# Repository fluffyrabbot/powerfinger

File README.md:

# PowerFinger

**Open-source assistive input devices. Under $25 BOM. Build one for anyone who
needs it.**

PowerFinger is a family of wearable and handheld pointing devices designed for
accessibility, repairability, and surface agnosticism. Hardware design files —
schematics, PCB layouts, 3D models, BOMs, and assembly docs — are published
under CERN-OHL-S 2.0. Firmware and software, including the companion app, are
published under MIT.

**Primary validation claim:** a user with limited wrist mobility can browse,
click, drag, and scroll on everyday surfaces without host-side remapping
software.

## Philosophy

Computer input is a solved problem for people who can sit at a desk and grip a
mouse. For everyone else — people with limited wrist mobility, repetitive strain
injuries, tremors, amputations, arthritis, or simply no desk — it isn't.

Existing assistive input devices cost $100–$350 and are closed, proprietary, and
fragile. When the vendor disappears, the device becomes e-waste and the user
loses their interface to the digital world.

PowerFinger treats input devices as **prosthetics for digital agency**. The more
redundant ways people have to control things the way they find most natural, the
better as a common good. We design for:

- **Affordability.** $9–$25 BOM depending on variant. The cheapest ring is under
  $10 in components. The first two-ring validation lane targets ~$24 total.
- **Universal design.** Every device works for able-bodied users at their desk
  AND for users with specific accessibility needs. No separate "disability"
  product line.
- **Surface agnosticism as a spectrum.** The optical ring works on most opaque
  surfaces (not glass). The ball+Hall variants are intended for glass, fabric,
  and skin, but those claims stay provisional until the surface protocol is run.
  The IMU variant needs no surface at all. Each variant's limitations are
  documented honestly — see
  [docs/COMBINATORICS.md](docs/COMBINATORICS.md).
- **Composability.** One ring is a mouse. Two rings are a mouse + scroll wheel.
  Three rings are a configurable control surface. The system grows with the
  user's needs.
- **Repairability.** Every part is replaceable. 3D-print a new shell, swap a
  battery, reflash firmware. No planned obsolescence.
- **Privacy.** Fully offline operation. No cloud, no telemetry, no account. Your
  movement data stays on your device.

## Active Program

### Active Validation Lane

- `R30-OLED-NONE-NONE` optical ring pair plus `USB-HUB`
- Goal: prove the no-host-remapping cursor + click + scroll workflow first
- Source of truth: [docs/ACTIVE-LANE-CHECKLIST.md](docs/ACTIVE-LANE-CHECKLIST.md)

### Hedge Lane

- `WSTD-BALL-NONE-NONE` wand
- Use this lane only after the active ring + hub lane clears its gates or if
  the ring fails package-closure / safety reality in a way that forces a
  productization pivot

### Deferred Until Gate 6

- Ball+Hall ring
- Puck variants
- Pro optical-on-ball ring
- OCR / camera and other rich companion features
- IMU hybrids and additional mountings beyond defensive publication coverage

## Form Factors

### Ring

Every ring has a tracking sensor + a click switch + BLE. One ring is the
single-device control loop. Two identical rings plus the hub are the primary
validation lane for the no-host-remapping workflow: cursor + left click on one
finger, scroll + right click on the other. Roles are assigned in software, not
hardware.

```
Middle finger (Ring 1):  move cursor + left click
Index finger  (Ring 2):  scroll      + right click
```

Everything else — drag, double-click, zoom, middle click, modifiers — is
software-defined combinations of those four primitives.

| Variant | BOM | Surface | Resolution |
|---------|-----|---------|------------|
| Optical ring (P0) | ~$9 | Most opaque surfaces (not glass) | 800–2000 CPI |
| Ball+Hall ring (P1) | ~$11 | Target: glass, fabric, skin, and other hard cases | ~15–60 DPI |
| Optical-on-ball ring (Pro) | ~$17 | Target: any rollable surface, pending validation | Up to 12,000 CPI |

Only the optical ring is in the active validation lane. The other ring variants
remain documented for defensive publication and later research.

A USB hub dongle (~$6) is the intended path for composing two or more rings into
a single USB HID mouse without host-side remapping software.

### Wand

A pen-shaped BLE HID pointing device with a ball+Hall sensor at the tip. This
is the hedge lane: a handheld form factor designed for the surfaces and angles
that defeat optical pen mice. It is not the primary validation lane while the
ring + hub proof remains red. ~$14 BOM.

No existing product fills this space. Commercial pen mice ($35–150) use optical
sensors that fail on glass and degrade past ~20 degrees of pen tilt. Assistive
styluses only work on touchscreens. The wand is designed to work across glass,
fabric, blankets, tray tables, and other accessibility-relevant surfaces at
natural pen angles (30–70 degrees), but those claims stay gated until the
hardware protocol is run.

Pen grip reduces forearm pronation from ~42 degrees (flat mouse) to ~28 degrees
— clinically significant for carpal tunnel and RSI. An aluminum or stainless
steel body provides natural weight stabilization for tremor (same principle as
weighted assistive pens).

See [docs/WAND-COMPETITIVE.md](docs/WAND-COMPETITIVE.md) for the competitive
landscape, accessibility case, and patent analysis.

### Other Mountings

The electronics module is invariant; the harness adapts it to any body position.
The ring shell is just one harness. Others: toe ring, knuckle strap, wrist
bracelet, prosthetic mount, headband. Same PCB, same firmware, different
physical mounting. The companion app assigns meaning. These remain design-space
and defensive-publication coverage, not active implementation work.

See [docs/COMBINATORICS.md](docs/COMBINATORICS.md) for the full design space.

## Sensing Mechanisms

| Mechanism | Surface Agnostic? | Moving Parts | BOM | Resolution |
|-----------|-------------------|-------------|-----|-----------|
| Mechanical ball + Hall effect | Target: glass, fabric, skin, and other rollable surfaces | Yes | ~$2 | Low (9–36 ticks/rev) |
| Direct optical (LED) | Most opaque surfaces | None | ~$0.50–4 | Good (800–2000 CPI) |
| Direct laser (VCSEL) | More surfaces than LED | None | ~$2–5 | Good (2000+ CPI) |
| Optical on captive ball | Target: any rollable surface, pending validation | Ball only | ~$5–8 | Excellent (12K CPI) |

## Deferred Capabilities

- **OCR camera** — scan text from physical books/documents, send to companion
  app for local OCR (Tesseract/PaddleOCR), translation, or text-to-speech.
  Requires companion app; pointing function works without it. Deferred until the
  active validation lane clears Gate 4.
- **Guidance laser** — red dot on the surface shows exactly where you're
  pointing/scanning. Deferred until the active validation lane clears Gate 4.

## What Exists Today

PowerFinger is still pre-prototype, but the repo already has a real software
lane. The main difference across directories is how much of each lane is
implementation versus planning:

| Area | Current reality | Start here |
|------|-----------------|-----------|
| Firmware | Real ESP-IDF targets exist for `ring`, `hub`, `pen`, and `puck`; the verifier covers its own regression tests, host tests, companion protocol, sanitizers, active R30 profile, hub, and strict KiCad by default. | `scripts/verify-firmware-local.sh`, `docs/FIRMWARE-VERIFY-LOCAL.md` |
| Companion | A minimal local Web Serial app now lives under `companion/web/`. It talks to the hub's existing USB CDC text protocol and covers hub info, role assignment, swaps, forget, hub settings, per-ring tuning, live RSSI plus battery/diagnostics inspection, and hub-owned simultaneous-click gesture mapping. | `companion/README.md`, `companion/web/`, `docs/COMPANION-APP-ARCH.md` |
| Hardware | BOM intent files still anchor the lane, and each BOM-backed variant now has a hardware publication packet with a manifest plus assembly/disassembly baseline. The active `R30-OLED-NONE-NONE` ring and `USB-HUB` now also have first-board checklists and validation templates alongside their KiCad/OpenSCAD skeletons; routed PCBs and measured hardware evidence are still pending. | `hardware/README.md`, `hardware/bom/README.md` |
| Docs | Design, validation, accessibility, and IP docs are the most complete part of the repo today. | `docs/` |

## Quick Start

Install CMake, a C compiler, Python, Ruby, Node.js, and KiCad CLI for full local
verification. See [prerequisites and modes](docs/FIRMWARE-VERIFY-LOCAL.md).
Then install the pinned SDK and verify (reports go under `build-verification/`):

```bash
scripts/setup-esp-idf-local.sh
scripts/verify-firmware-local.sh
```

After the one-time bootstrap, `scripts/verify-firmware-local.sh` can run from a
fresh shell and will auto-activate the repo-pinned ESP-IDF 6.1 build candidate.
[Physical hardware qualification remains pending](docs/ESP-IDF-6.1-QUALIFICATION.md).
If you want `idf.py` available in your current shell for direct iteration, run:

```bash
eval "$(scripts/setup-esp-idf-local.sh --export)"
```

The shared verifier runs all mandatory local checks and builds the active
`R30-OLED-NONE-NONE` ring profile and hub. To include the generic development
ring, pen, and puck as well:

```bash
scripts/verify-firmware-local.sh --all
```

For host/contracts/operator/companion checks without SDK or hardware:

```bash
scripts/verify-firmware-local.sh --fast
```

For prerequisite diagnostics without builds:

```bash
scripts/verify-firmware-local.sh --doctor
```

For the local companion app scaffold:

```bash
scripts/serve-companion-local.sh
```

Then open `http://127.0.0.1:4173` in Chrome or Edge and connect to the hub over
Web Serial.

For hardware CAD work on macOS, prefer the current OpenSCAD snapshot cask:

```bash
brew install --cask openscad@snapshot
```

The executable remains `openscad` on `PATH`. Avoid relying on the legacy
`brew install openscad` cask path; Homebrew currently marks that older cask as
deprecated while the snapshot cask tracks the current upstream builds.

See [docs/ACTIVE-LANE-CHECKLIST.md](docs/ACTIVE-LANE-CHECKLIST.md) for the
canonical active-lane checklist, [docs/FIRMWARE-VERIFY-LOCAL.md](docs/FIRMWARE-VERIFY-LOCAL.md)
for the local verification flow, [docs/PROTOTYPE-SPEC.md](docs/PROTOTYPE-SPEC.md)
for the active build spec, [docs/COMBINATORICS.md](docs/COMBINATORICS.md) for
the broader design space, and [docs/GO-NO-GO-RUBRIC.md](docs/GO-NO-GO-RUBRIC.md)
for the validation gate order.

## Project Status

**Pre-prototype.** Architecture, design space, power budget, and competitive
analysis are documented, and the repo already contains real firmware projects
plus a local verification path. Active scope is frozen to the optical ring +
hub validation lane, with the wand as the hedge lane. The companion lane now
has a minimal local Web Serial scaffold, while the hardware tree contains BOM-
backed publication packets, service baselines, first-pass source skeletons, and
active-lane first-board checklists for the ring + hub proof path rather than
finished CAD/PCB drops. See
[docs/ACTIVE-LANE-CHECKLIST.md](docs/ACTIVE-LANE-CHECKLIST.md) for the current
program order and [docs/FIRMWARE-ROADMAP.md](docs/FIRMWARE-ROADMAP.md) for the
firmware build order that runs on dev boards before prototype hardware arrives.

## License

Three artifacts, three licenses:

- **Hardware designs** (schematics, PCB layouts, 3D models, BOMs, assembly
  docs): [CERN-OHL-S 2.0](https://opensource.org/license/cern-ohl-s)
  (strongly reciprocal). See [LICENSE-HARDWARE](LICENSE-HARDWARE).
- **Firmware and software** (ESP-IDF code, companion app): MIT.
  See [LICENSE-SOFTWARE](LICENSE-SOFTWARE).
- **Documentation** (`docs/*.md`, READMEs, assembly guides):
  [CC-BY-SA 4.0](https://creativecommons.org/licenses/by-sa/4.0/).
  See [LICENSE-DOCS](LICENSE-DOCS).

The CERN-OHL-S patent retaliation clause means anyone using these designs who
sues anyone else over them automatically loses their license. The reciprocal
requirement means anyone manufacturing products from these designs must publish
their complete source. See [docs/IP-STRATEGY.md](docs/IP-STRATEGY.md) for full
rationale.

**"PowerFinger" is used descriptively. No trademark is asserted by the
maintainers.** Anyone may build, sell, and modify the design under the
licenses above. Derivative makers are encouraged to use their own product
name and pursue [OSHWA Certified](https://certification.oshwa.org/) status as
a third-party quality signal. See
[docs/NAMING-AND-COMPATIBILITY.md](docs/NAMING-AND-COMPATIBILITY.md) for the
full naming-and-compatibility posture.

## Why "PowerFinger"?

Controlling a computer should require nothing more than a single finger. The
name is corny. It sticks.

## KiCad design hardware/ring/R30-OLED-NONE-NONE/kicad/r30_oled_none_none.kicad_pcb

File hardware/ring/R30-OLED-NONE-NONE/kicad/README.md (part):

<!-- SPDX-License-Identifier: CERN-OHL-S-2.0 -->
# R30-OLED-NONE-NONE KiCad Skeleton

This directory is the PCB/schematic starting point for the active optical ring
lane. It is intentionally honest about its state: the first routed PCB pass now
exists, and the power/USB plus MCU/radio plus sensor/click sheets now include
first-pass symbols. The current KiCad wrapper snapshot is ERC/DRC/parity clean,
but fabrication outputs and physical first-board evidence are still separate
packet gates.

## Current Source Files

- `r30_oled_none_none.kicad_sch` — root sheet for the active optical ring lane
- `r30_oled_none_none.kicad_pcb` — first rigid P0 routed board pass, with
  footprint locks, placement zones, antenna keep-outs, and charge-path routing
- `FABRICATION-OUTPUTS.md` — local Gerber/drill/POS plus active-BOM/POS review
  commands, hashes, and caveats for the DRC-clean first-board source
- `BOARD-HOUSE-OUTPUT-CONSTRAINTS.md` — prototype-house intake checklist for
  turning the local outputs into specific pre-fab feedback without claiming
  physical ring closure
- `sheets/power_and_charge.kicad_sch`
- `sheets/mcu_radio.kicad_sch`
- `sheets/sensor_and_click.kicad_sch`
- `sheets/usb_and_service.kicad_sch`

## What Belongs Here Next

- Local symbol and footprint references only where upstream libraries are not
  enough
- Plot and fabrication presets once routing exists
- `INTERFACE-CONTRACT.md` — first-pass electrical pin contract for capture and firmware
- `CAPTURE-BINDINGS.md` — which active BOM lines need stock, vendor, or custom binding
- `SCHEMATIC-CAPTURE.md` — sheet split, net naming, and capture order
- `BOM-BLOCK-MAP.md` — turn the BOM into schematic blocks without drift
- `RECOMMENDED-FIRST-CAPTURE.md` — the recommended P0 scope boundary
- `../FIRST-BOARD-CHECKLIST.md` — the execution checklist that decides when this
  packet is allowed to move on to secondary variants

## Capture Order

1. Power tree: protected LiPo, TP4054 charge path, RT9080 LDO, fixture-fed
   VBUS service jumper, NTC divider
2. MCU/module block: `ESP32-C3-MINI-1-N4` with antenna keep-out reserved first
3. Sensor block: PAW3204-class optical sensor plus matching lens and aperture
4. Human input block: dome switch and any required debounce/passive support
5. Off-board USB service/programming path for charging plus firmware bring-up

## First Routed Board Pass

`r30_oled_none_none.kicad_pcb` locks the current P0 direction:

- rigid validation board with separate power/service, sensor/click, and
  MCU/radio zones
- ESP32-C3-MINI-1 antenna end facing the shell exterior, with copper and
  antenna keep-outs marked before any convenience routing; the external
  keep-out forbids tracks, vias, pads, and copper pour while allowing the owning
  module footprint whose antenna courtyard reaches the board edge
- bottom-side PAW3204 placement centered on the `6.2 mm` optical aperture datum
  recorded as a `Cmts.User` alignment circle, not an internal `Edge.Cuts`
  fabrication cutout through the populated PCB
- off-board same-net battery service pads for a replaceable protected-cell
  harness or fixture; no onboard JST-SH receptacle body is claimed
- Off-board same-net USB service pads for USB2 data, VBUS, CC pulldowns, GND,
  and shield continuity; charge/program service now requires a fixture or pogo
  harness rather than an onboard USB-C receptacle
- TP4054 path routed through a non-BOM fixture-fed VBUS service jumper,
  `20 kohm` RPROG, RT9080 regulation, and an NTC divider near the battery
  service pads
- MCU/radio and sensor/click sheets populated with first-pass symbol
  counterparts for the routed `U1`, `U2`, `SW1`, decoupling, sense testpads,
  and sensor bring-up pads
- routed sheet nets promoted to passive global labels where they intentionally
  match flat PCB net names, with the project-local `Q1` VBUS service jumper,
  aligned USB ESD D+/D- labels, and service shield pads mapped to `SH`
- `J_BAT` backed by a project-local first-board symbol that models `MP1`/`MP2`
  as GND-tied shield/service pads, so schematic/PCB parity is clean
- first routing cleanup of USB-C SMT contact pad length, snap-dome contact
  geometry, and wrong first-pass power/USB endpoint coordinates
- second routing cleanup of the SDIO/motion fanout, VBUS-detect dogleg, long
  VBUS detector feed, and minimum routed trace width
- charger-service cleanup that replaces the active `Q1`/`R4`/`Q2`/`R6`
  charge-gate with a non-BOM fixture-fed VBUS jumper into TP4054 `VCC`
- USB/D1 fanout cleanup that nudges `D1` upward, doglegs J1 `A6`/`A7` before
  the drop, and separates the long `USB_D+`/`USB_D-` lanes into U1
- connector-edge cleanup that extends the fixed J1 service lip leftward and
  ties J1 `A4`/`A9`/`B4`/`B9` as one VBUS contact group
- connector-cluster cleanup that moves `R2B` beside J1 `B5`, shifts the local
  VBUS trunk inward, and moves `NTC1`/`R3` out of D1's immediate `USB_D+`
  corridor
- A-side USB data cleanup that moves the J1 `A6`/`A7` to D1 escape onto `B.Cu`
  under the charger cluster and re-enters beside D1 with the `USB_D-` entry via
  shifted left for clearance
- mirrored USB-C data cleanup that routes J1 `B6`/`B7` into the same escape
  through separated `B.Cu` lanes and a short front-layer `USB_D-` overpass,
  while leaving D1 VBUS disconnected because the direct branch still regresses
  total DRC; route-only D1 GND/VBUS service-island attempts also regress, so the
  follow-up needed footprint/placement movement rather than another local
  stitch
- D1 footprint cleanup that replaces the rail-clamped USBLC6 SOT-23-6 island
  with a rail-less TPD2E2U06DCK-class SC-70/SOT-323 data-line shunt, removing
  the D1 VBUS branch from the constrained service-edge pocket
- service-edge GND/shield spine that ties the J1 ground contacts and shell
  stakes, pulls `R2B` and `R1` into the lower return, reaches `J_BAT` `MP1`
  from the upper return, and drops D1/NTC ground through a local B-side via
  without reintroducing VBUS-clamped ESD protection
- battery-side GND fanout cleanup that doglegs `R8`/`J_BAT` `MP2` away from
  the `VBAT_SENSE` trace, ties `J_BAT` pad 2 into that local return, moves
  `J_BAT` `MP1` onto a B-side return via, and joins `R2A`/left `SW1`/`Q2`
  source into one local ground chain
- via-rule cleanup that brings the six remaining sub-minimum first-board vias
  from `0.46` mm diameter / `0.20` mm drill to the board-rule minimum
  `0.50` mm diameter / `0.30` mm drill
- sensor-rail cleanup that moves the `VREG_3V3` via off the PAW3204
  `SENSOR_LED_KIT`/GND pad column, routes the sensor `VDD`/`VDDA` feed down a
  right-side `B.Cu` trunk, and keeps `C1B` tied in with a short local branch
- `TP_LEDKIT` contract cleanup that supersedes the earlier PAW3204 LED test-pad
  move by deleting the non-BOM pad/stub and leaving the PAW3204 LED-kit pin as
  an explicit local no-connect
- U3 VBAT escape cleanup that routes TP4054 BAT around the GND/CHRG pad row
  through an outer dogleg before rejoining the U4 VIN trunk
- C2 input-cap placement cleanup that moves and micro-retargets the 10uF
  capacitor closer to U4 VIN while leaving its GND pad as an honest unconnected
  blocker
- B-side sensor-pocket cleanup that reroutes the `C1B` ground return around the
  PAW3204 LED pad column without moving the shell-bound PAW3204 aperture
- C1A MCU-side decoupler cleanup that moves the non-shell-bound capacitor into
  the U1 `3V3` / `GND1` pocket while leaving the shell-bound `SW1` and U1
  placements fixed
- `TP_VBAT` / right-SW1 cleanup that reroutes `VBAT_SENSE` below the top dome
  ground pad and ties the right `SW1` ring pad into the local U1/C1A ground leg
- SW1 click cleanup that reroutes `CLICK_PRIMARY_N` through a B-side via pair
  instead of through the lower dome ground pad
- C1B/U2 B-side GND cleanup that doglegs around the PAW3204 LED pad column
  without moving the shell-bound sensor aperture
- R1 charger-programming cleanup that moves non-shell-bound `R1` into a
  horizontal pocket and returns its GND pad through the accepted B-side trunk
- U4 regulator-pocket cleanup that nudges non-shell-bound U4 while preserving
  the accepted C2 placement and U3 `VBAT_PROTECTED` dogleg
- D1/NTC ground-return cleanup that moves the local GND leg through a B-side
  dogleg so it no longer shorts the `NTC_SENSE` divider trace
- `TP_VBAT` micro-retarget that moves the sense test pad upward and removes the
  upper `SW1`/`VBAT_SENSE` short
- left-service silkscreen cleanup that moves the dense `J_BAT`, `Q1`, `R8`,
  and `R2A` reference fields to `F.Fab` instead of printing clipped labels over
  the bring-up pads/copper
- `R2A` placement cleanup that moves the CC1 pull-down to `(111.650, 95.000)`
  and retargets its `USB_CC1_RD` plus GND endpoints, clearing the
  `USB_CC1_RD` / `CHARGE_GATE` short without changing ERC, unconnected count,
  or schematic/PCB parity
- `VBAT_SENSE` divider-junction cleanup that retargets the `R7`/`R8`/`TP_VBAT`
  sense trunk through `(113.000, 91.900)`, clearing the upper `SW1` dome-ring
  short without moving shell-bound `SW1` or the CAD dome pocket
- `SW1` / `VBAT_SENSE` topology cleanup that lowers the divider junction to
  `(113.000, 92.100)` and moves the serviceable dome plus shell pocket to
  `(114.200, 95.300)`, reducing total DRC while keeping shorts closed
- top-edge `VBUS_5V` trunk cleanup that retargets the VBUS feed from
  `(105.820, 91.600)` to `(105.600, 91.600)`, clearing the `J_BAT` `MP1`
  short without moving the then-shell-bound battery connector
- in-place `R9` divider flip so the right-side `VBUS_5V` trunk lands on the
  VBUS pad and `VBUS_DETECT` exits the opposite pad into the existing top node,
  plus moving `R9`'s source reference field to `F.Fab` in the copper-dense
  divider pocket
- `SW1` dome-pocket relief that moves the shell-bound click center down to
  `(114.350, 95.780)` and moves the CAD dome pocket with it; this established
  the earlier short-free topology that later ground-continuity and
  three-contact dome-ring closures brought to the current verified
  `DRC=40`, `unconnected=0`, parity `0` snapshot
- non-shell-bound `R11` / `TP_CHRG` relocation down into the charger-status
  pocket at `y=105.000`, shortening the `CHRG_STAT` run and moving their source
  reference fields to `F.Fab` in the dense regulator pocket
- top-edge source-label cleanup that keeps the accepted `VBUS_5V` /
  `VBAT_SENSE` copper after scratch retargets introduced shorting or edge debt,
  and moves the `R7`, `TP_VBAT`, and `SW1` reference fields to `F.Fab`
- charge/regulator-pocket source-label cleanup that keeps the accepted
  `CHARGE_EN`, `VREG_3V3`, and `VBAT_PROTECTED` copper after scratch retargets
  reintroduced shorting or unconnected debt, and moves the `Q2`, `U4`, and `R6`
  reference fields to `F.Fab`
- left-service source-label cleanup that keeps the accepted `USB_CC1_RD`,
  `VBUS_5V`, and `CHARGE_GATE` copper after scratch CC1/gate reroutes
  reintroduced shorting or unconnected drift, and moves the `R4` and `R1`
  reference fields to `F.Fab`
- remaining source-label cleanup that keeps the accepted `NTC_SENSE`,
  `VREG_3V3`, and `CHRG_STAT` copper after scratch reroutes raised total DRC or
  reintroduced shorting, and moves the remaining source-only silkscreen marks
  to `F.Fab`/`B.Fab`
- pad-mask expansion cleanup that keeps `solder_mask_min_width=0.05` but
  changes first-board pad mask expansion from `0.05` to `0`, reducing
  mask-bridge rows without relaxing the minimum mask-web rule
- regulator/C2 spoke-width cleanup that keeps U4 and C2 placement fixed after
  scratch placement variants reintroduced shorts or held total DRC, and narrows
  the two `VBAT_PROTECTED` spokes from `0.32` to `0.24`
- Q1 left-service cleanup that rejects R4 orientation, CC1 dogleg, and
  top-edge `VBUS_5V`/`VBAT_SENSE` variants with unconnected, shorting, or
  copper-edge debt, then nudges Q1 upward by a retained total `0.30` mm and
  retargets its three local service endpoints
- TP_VBAT top power-pocket cleanup that rejects regulator width, R11/TP_CHRG,
  U4, R6, C2 GND, C1A, and layer-hop probes that held total DRC or added debt,
  then nudges `TP_VBAT` right by `0.10` mm and retargets its two local
  `VBAT_SENSE` endpoints
- SENSOR_SCLK MCU-column cleanup that rejects direct SCLK, top-dogleg SCLK,
  `VBUS_DETECT`, and `SENSOR_MOTION_N` route variants with shorts or clearance
  debt, then raises the local SCLK jog from `y=99.900` to `y=99.980`
- TP_MOT MCU-column cleanup that rejects VBUS spine, VBUS dogleg, B-side
  motion-hop, and right-of-VBUS `TP_MOT` variants with dangling vias, shorts,
  mask, or clearance debt, then moves `TP_MOT` to `(121.250, 99.500)` and
  retargets its local `SENSOR_MOTION_N` endpoint
- NTC sense-spine cleanup that rejects USB data-pair and broad `NTC_SENSE`
  trunk/layer-hop variants with shorts, clearance, mask, or track-width debt,
  then moves only the local `NTC_SENSE` junction from `(110.420, 106.700)` to
  `(109.900, 106.700)`
- Left-service CC2 pulldown cleanup that rejects VBUS doglegs, VBUS junction
  moves, and broad R2B shifts with shorts, copper-edge, hole-clearance, mask, or
  extra clearance debt, then moves only `R2B` from `(100.500, 101.500)` to
  `(100.400, 101.500)` and retargets its local `USB_CC2_RD` and GND endpoints
- GND-continuity cleanup that keeps the shell-bound placements and schematic
  contracts intact while closing six unconnected rows: a lower `SW1` local GND
  stitch, via-assisted U3 and C2 returns, a via-assisted `J_BAT` pad-2 return,
  a left-trunk B-side bridge, and a C2-to-U1-side GND return; direct `J1` A12
  and top-`SW1` closure variants were rejected because they reintroduced
  current shorting rows
- `J1` A12 service-ground cleanup that closes the lower USB-C ground row from
  the existing lower GND rail endpoint to the accepted service-edge via while
  leaving the USB-D- fanout intact; top-`SW1` closure remains blocked by the
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
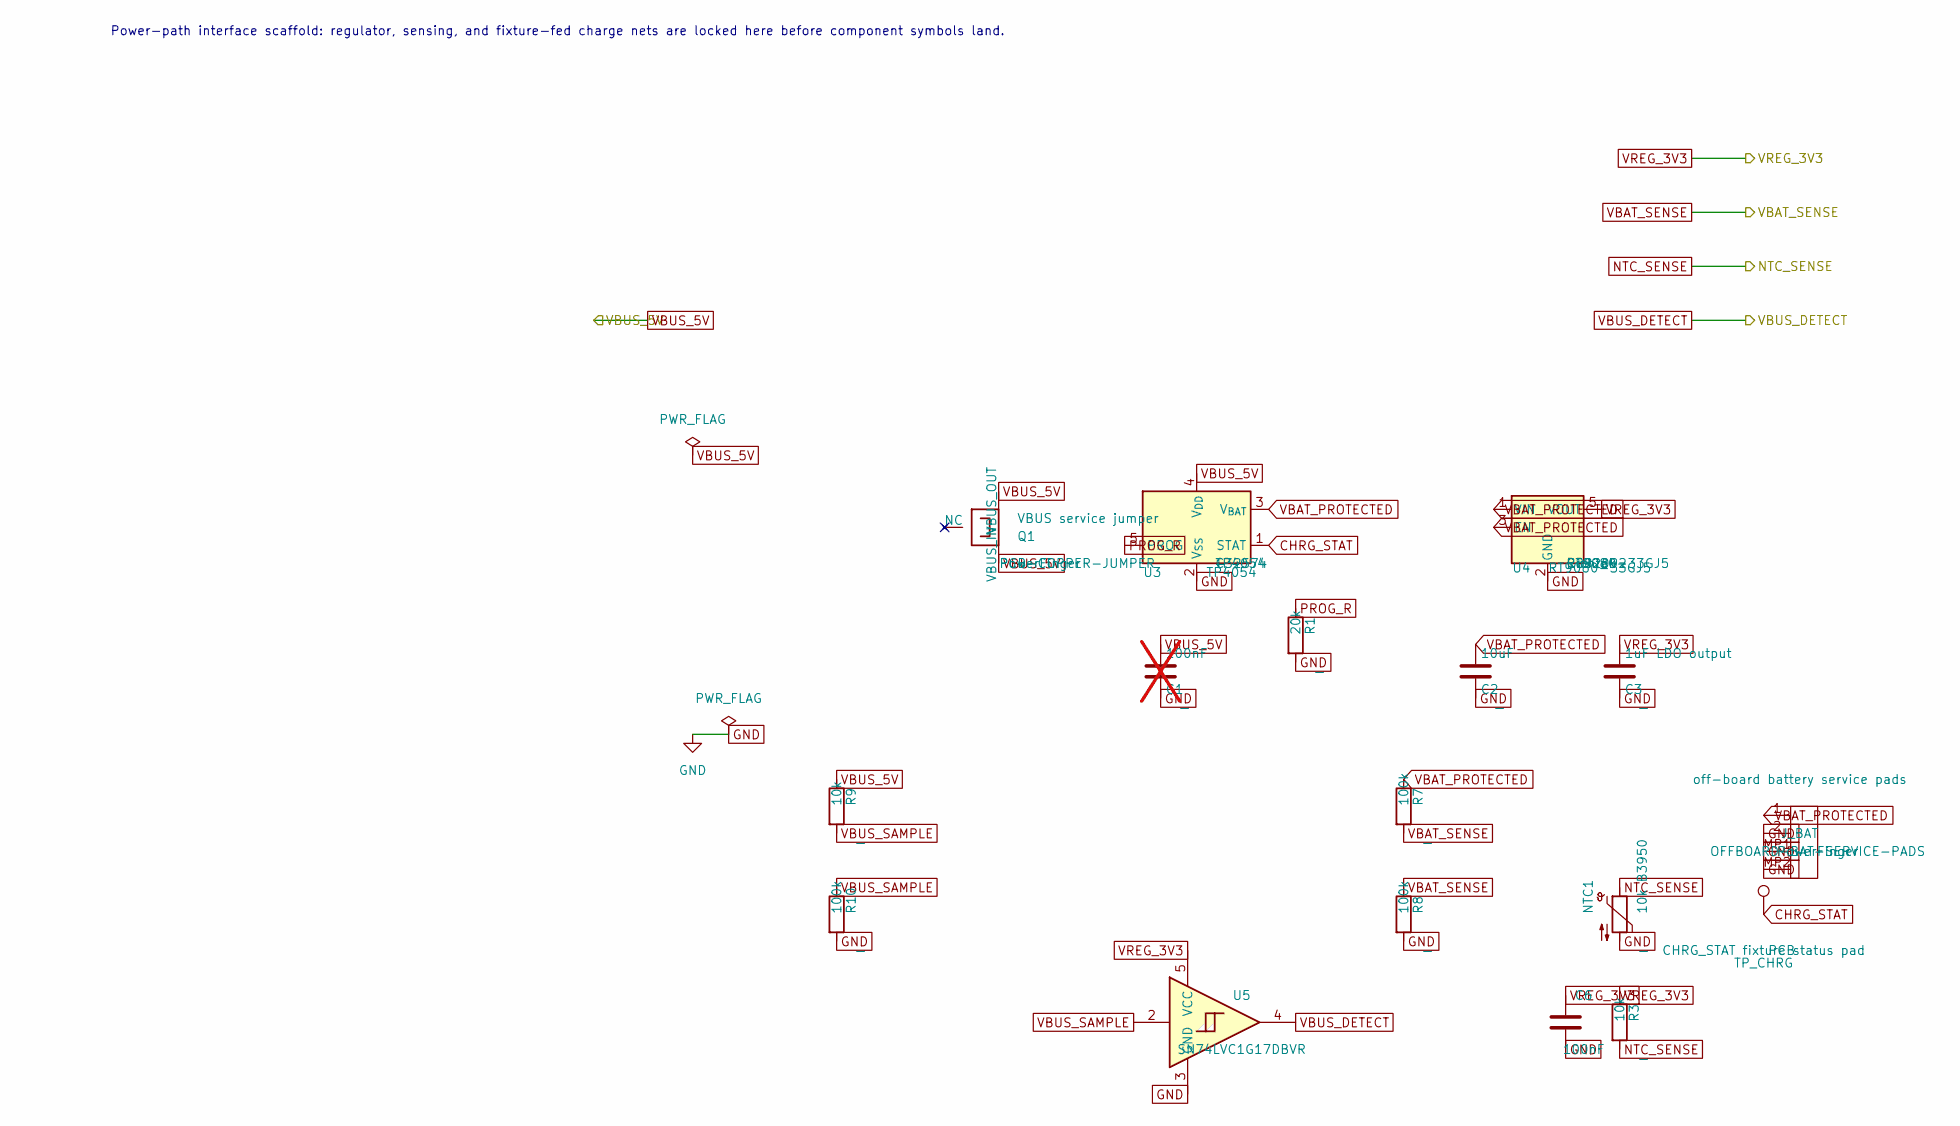
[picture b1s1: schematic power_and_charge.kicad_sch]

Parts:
C1: 100nF; C_0402_1005Metric; not fitted
C2: 10uF; C_0603_1608Metric
C3: 1uF LDO output; C_0603_1608Metric
C6: 100nF; C_0402_1005Metric
J_BAT: off-board battery service pads; Offboard_Battery_Service_SameNet; mfg_part_num OFFBOARD-BAT-SERVICE-PADS
NTC1: 10k B3950; Thermistor_NTC_0402_1005Metric
Q1: VBUS service jumper; VBUS_Service_Jumper_SOT23Land; mfg_part_num PCB-COPPER-JUMPER
R1: 20k; R_0402_1005Metric
R3, R9: 10k; R_0402_1005Metric
R7, R8, R10: 100k; R_0402_1005Metric
TP_CHRG: CHRG_STAT fixture status pad; TestPoint_Pad_D1.0mm_FirstBoard
U3: TP4054; SOT-23-5; mfg_part_num TP4054; lcsc C32574
U4: RT9080-33GJ5; RT9080_33GJ5_SOT23_5_ServiceClearance; mfg_part_num RT9080-33GJ5; lcsc C882092
U5: SN74LVC1G17DBVR; SOT-23-5

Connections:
CHRG_STAT: TP_CHRG.1, U3.1 (CHRG)
NTC_SENSE: NTC1.1, R3.2; also elsewhere on the board
PROG_R: R1.1, U3.5 (PROG)
VBAT_PROTECTED: C2.1, J_BAT.1 (VBAT+), R7.1, U3.3 (BAT), U4.1 (VIN), U4.3 (EN)
VBAT_SENSE: R7.2, R8.1; also elsewhere on the board
VBUS_DETECT: U5.4; also elsewhere on the board
VBUS_SAMPLE: R9.2, R10.1, U5.2
VREG_3V3: C3.1, C6.1, R3.1, U4.5 (VOUT), U5.5 (VCC); also elsewhere on the board

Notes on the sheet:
Power-path interface scaffold: regulator, sensing, and fixture-fed charge nets are locked here before component symbols land.

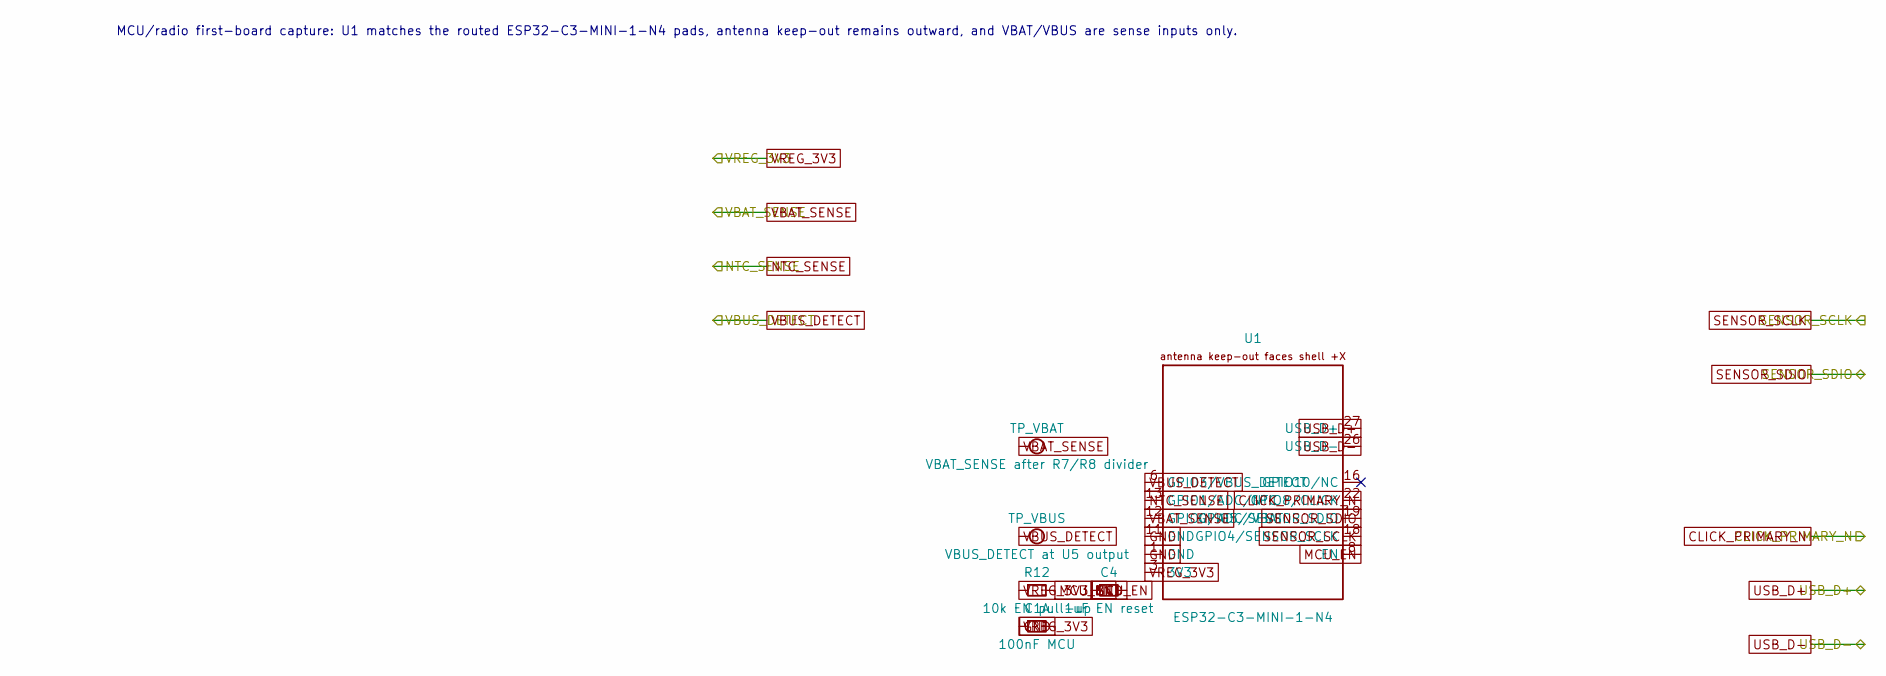
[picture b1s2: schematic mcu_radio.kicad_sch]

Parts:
C1A: 100nF MCU; C_0402_1005Metric
C4: 1uF EN reset; C_0603_1608Metric
R12: 10k EN pull-up; R_0402_1005Metric
TP_VBAT: VBAT_SENSE after R7/R8 divider; TestPoint_Pad_D1.0mm
TP_VBUS: VBUS_DETECT at U5 output; TestPoint_Pad_D1.0mm
U1: ESP32-C3-MINI-1-N4; ESP32-C3-MINI-1_N4_Module_P0_AntennaRight

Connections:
CLICK_PRIMARY_N: U1.22 (GPIO8/CLICK); also elsewhere on the board
MCU_EN: C4.1, R12.2, U1.8 (EN)
NTC_SENSE: U1.13 (GPIO1/ADC/NTC); also elsewhere on the board
SENSOR_SCLK: U1.18 (GPIO4/SENSOR_SCLK); also elsewhere on the board
SENSOR_SDIO: U1.19 (GPIO5/SENSOR_SDIO); also elsewhere on the board
USB_D+: U1.27 (USB_D+); also elsewhere on the board
USB_D-: U1.26 (USB_D-); also elsewhere on the board
VBAT_SENSE: TP_VBAT.1, U1.12 (GPIO0/ADC/VBAT); also elsewhere on the board
VBUS_DETECT: TP_VBUS.1, U1.6 (GPIO3/VBUS_DETECT); also elsewhere on the board
VREG_3V3: C1A.1, R12.1, U1.3 (3V3); also elsewhere on the board

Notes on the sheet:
MCU/radio first-board capture: U1 matches the routed ESP32-C3-MINI-1-N4 pads, antenna keep-out remains outward, and VBAT/VBUS are sense inputs only.

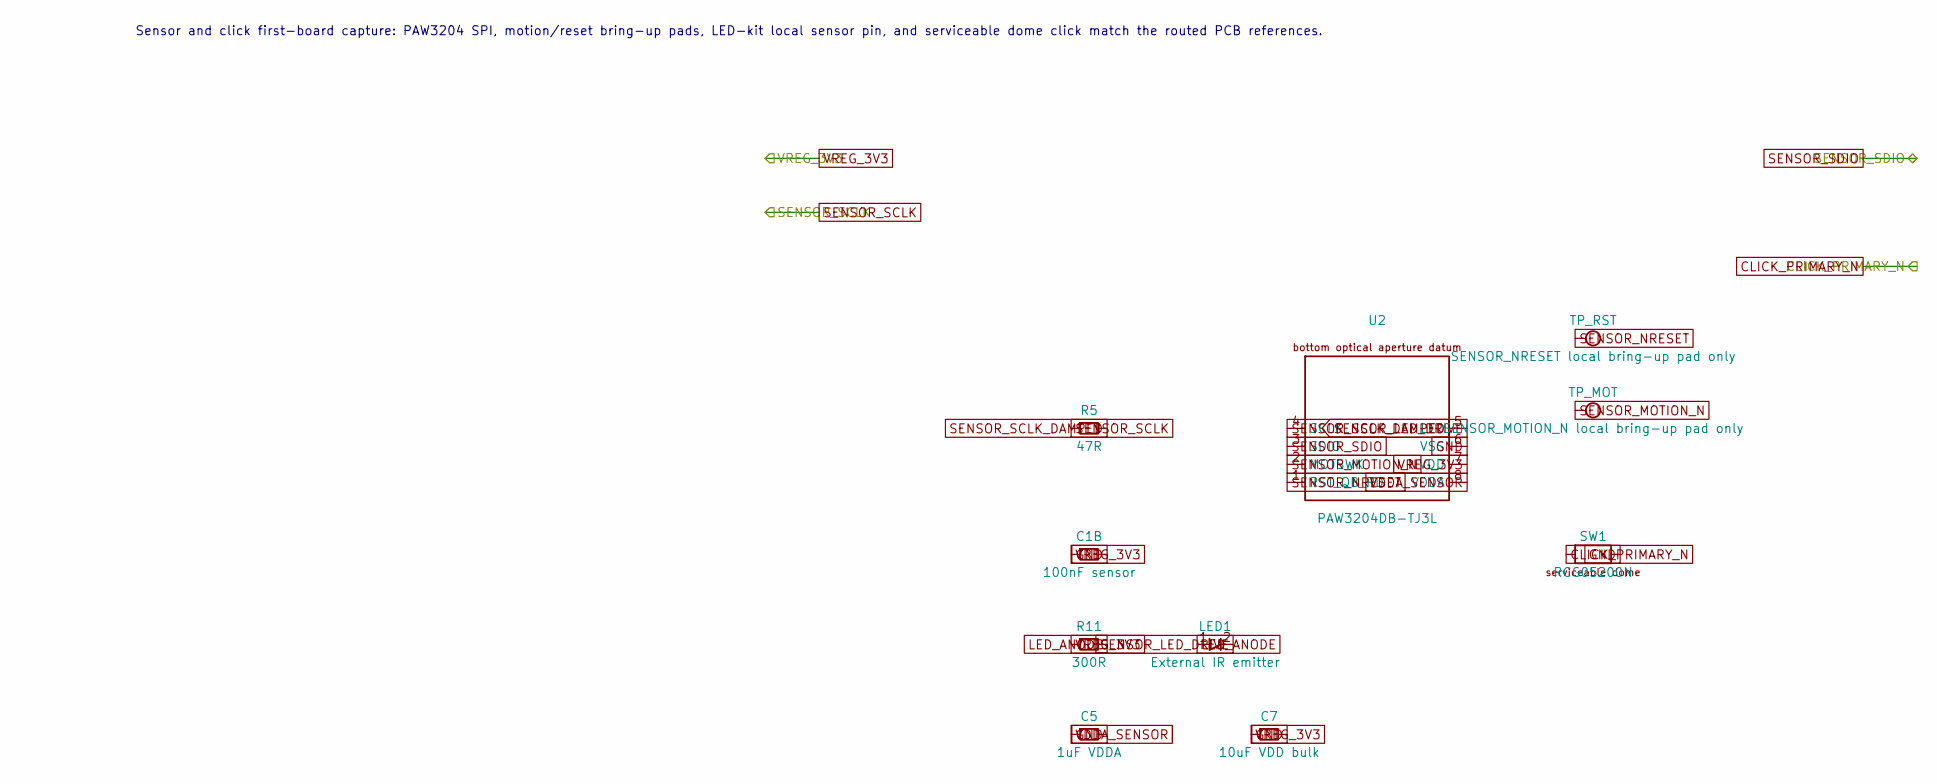
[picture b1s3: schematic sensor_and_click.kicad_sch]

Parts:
C1B: 100nF sensor; C_0402_1005Metric
C5: 1uF VDDA; C_0402_1005Metric
C7: 10uF VDD bulk; C_0603_1608Metric
LED1: External IR emitter; IR_Emitter_Lead_Pads
R5: 47R; R_0402_1005Metric
R11: 300R; R_0402_1005Metric
SW1: RCG05200N; Snap_Dome_5mm_TwoPad_Serviceable
TP_MOT: SENSOR_MOTION_N local bring-up pad only; TestPoint_Pad_D1.0mm
TP_RST: SENSOR_NRESET local bring-up pad only; TestPoint_Pad_D1.0mm
U2: PAW3204DB-TJ3L; PAW3204DB_TJ3L_Staggered_DIP8_Bottom_ApertureDatum

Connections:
CLICK_PRIMARY_N: SW1.1 (DOME_CENTER); also elsewhere on the board
LED_ANODE: LED1.1 (A), R11.2
SENSOR_LED_DRIVE: LED1.2 (K), U2.5 (LED)
SENSOR_MOTION_N: TP_MOT.1, U2.2 (MOTSWK)
SENSOR_NRESET: TP_RST.1, U2.1 (RST_QB_PD)
SENSOR_SCLK: R5.1; also elsewhere on the board
SENSOR_SCLK_DAMPED: R5.2, U2.4 (SCLK)
SENSOR_SDIO: U2.3 (SDIO); also elsewhere on the board
VDDA_SENSOR: C5.1, U2.8 (VDDA)
VREG_3V3: C1B.1, C7.1, R11.1, U2.7 (VDD); also elsewhere on the board

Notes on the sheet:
Sensor and click first-board capture: PAW3204 SPI, motion/reset bring-up pads, LED-kit local sensor pin, and serviceable dome click match the routed PCB references.

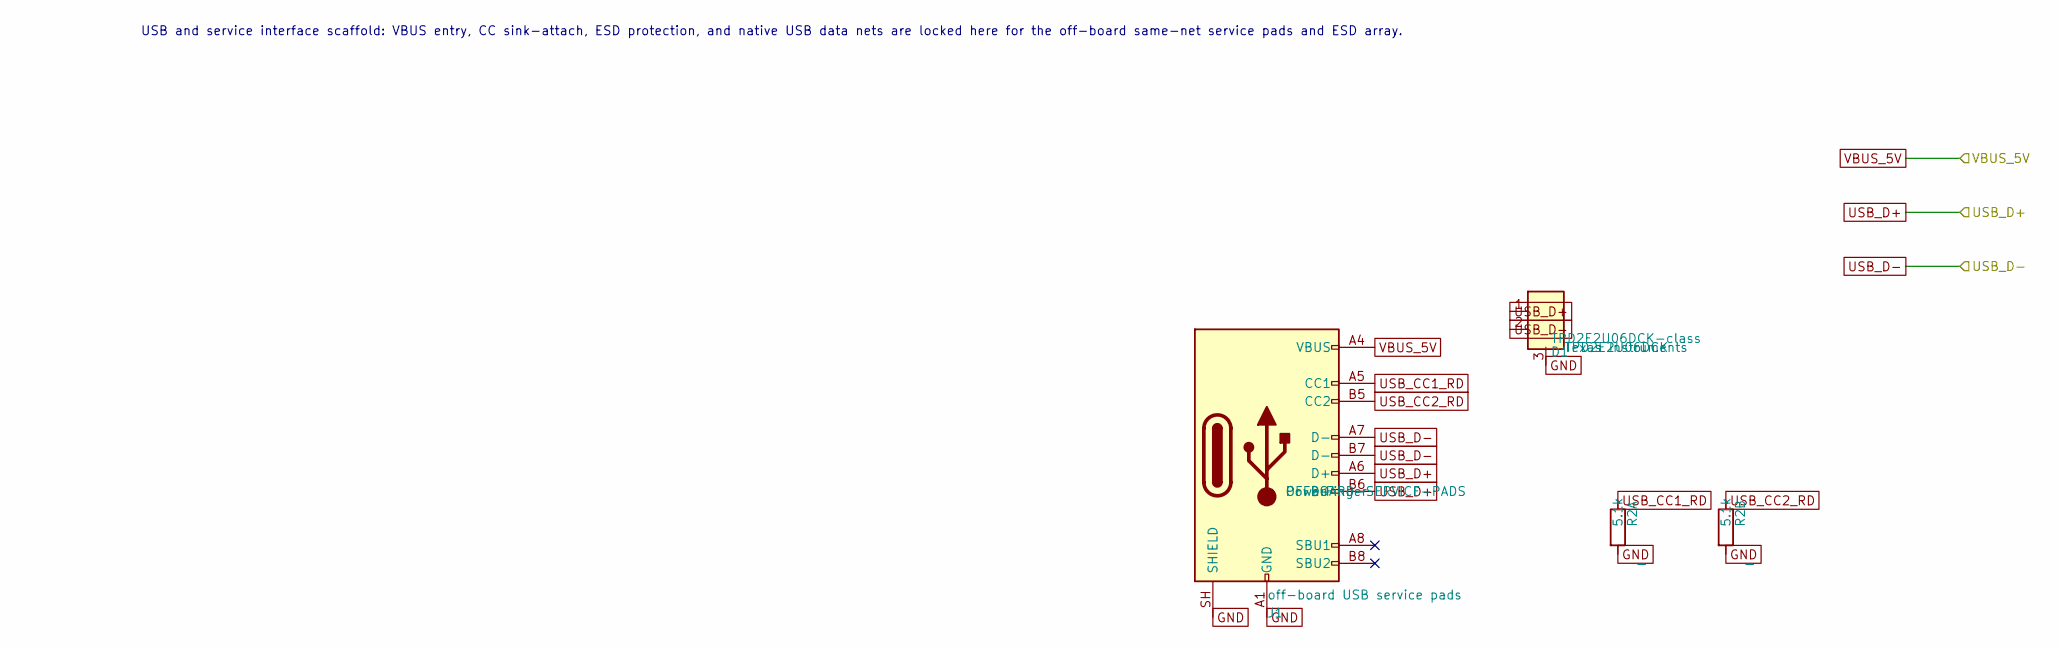
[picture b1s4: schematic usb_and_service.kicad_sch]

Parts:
D1: TPD2E2U06DCK-class; SOT-323_SC-70; mfg_part_num TPD2E2U06DCK
J1: off-board USB service pads; Offboard_USB_Service_SameNet; mfg_part_num OFFBOARD-SERVICE-PADS
R2A, R2B: 5.1k; R_0402_1005Metric

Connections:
USB_CC1_RD: J1.A5 (CC1), R2A.1
USB_CC2_RD: J1.B5 (CC2), R2B.1
USB_D+: D1.1 (IO1), J1.A6 (D+), J1.B6 (D+); also elsewhere on the board
USB_D-: D1.2 (IO2), J1.A7 (D-), J1.B7 (D-); also elsewhere on the board

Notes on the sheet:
USB and service interface scaffold: VBUS entry, CC sink-attach, ESD protection, and native USB data nets are locked here for the off-board same-net service pads and ESD array.

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
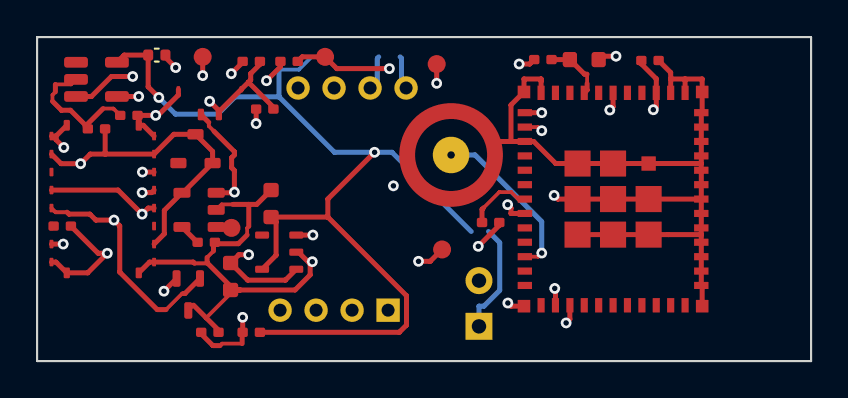
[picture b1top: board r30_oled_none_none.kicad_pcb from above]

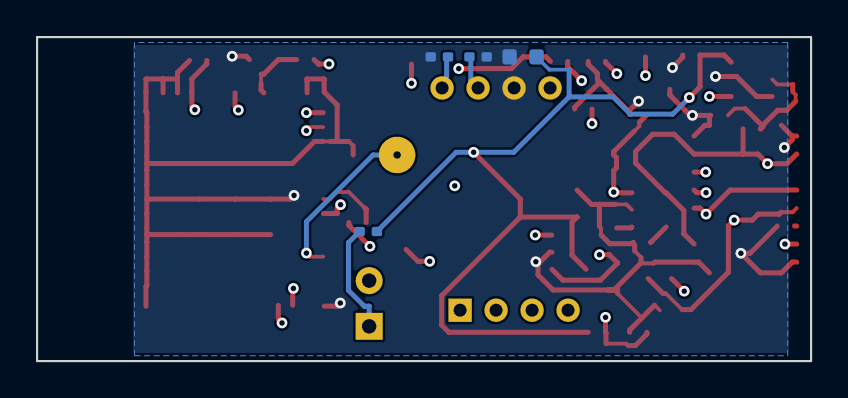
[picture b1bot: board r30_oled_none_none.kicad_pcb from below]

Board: 4 copper layers, 43.0 x 18.0 mm, 36 parts (6 on the bottom side), 24 nets.

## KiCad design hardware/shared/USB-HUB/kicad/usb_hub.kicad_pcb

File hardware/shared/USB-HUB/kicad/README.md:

<!-- SPDX-License-Identifier: CERN-OHL-S-2.0 -->
# USB-HUB KiCad Packet

This directory is the schematic/layout starting point for the active hub
accessory lane.

The packet now includes a first routed board-source pass. It is still a first
board, not measured hardware evidence: connector strain, host clearance, and
enclosure fit must be validated before the lane moves to secondary variants.

## Current Source Files

- `usb_hub.kicad_sch` — root sheet for the active hub lane
- `sheets/usb_and_power.kicad_sch`
- `sheets/mcu_radio.kicad_sch`
- `sheets/controls_and_indicators.kicad_sch`
- `usb_hub.kicad_pcb` — stepped USB-A direct-plug first-board pass
- `usb_hub.kicad_pro` — local KiCad project settings for this packet
- `sym-lib-table` — local project symbol table for KiCad CLI/library checks
- `PowerFinger.kicad_sym` — local hub-specific first-board symbols
- `fp-lib-table` — local project footprint table for KiCad CLI/library checks
- `PowerFinger_USB.pretty/` — local footprint library for the direct-plug USB-A
  connector, first-board ESP32-S3 module land pattern, service pads, clamp
  holes, and packet-pinned commodity footprints
- `FABRICATION-OUTPUTS.md` — checked-in note for regenerating and reviewing the
  local Gerber, drill, POS, active-BOM/POS, and archive outputs
- `BOARD-HOUSE-OUTPUT-CONSTRAINTS.md` — board-house intake questions tied to
  the current generated-output state

## What Belongs Here Next

- `INTERFACE-CONTRACT.md` — first-pass native USB and recovery-pin contract
- `BRINGUP-SERVICE-MATRIX.md` — mandatory recovery access and first-board checks
- `CAPTURE-BINDINGS.md` — which active BOM lines need stock, vendor, or custom binding
- `P0-COMPONENT-LOCKS.md` — exact first-board USB and power parts for the active dongle lane
- `SCHEMATIC-CAPTURE.md` — sheet split, net naming, and capture order
- `BOM-BLOCK-MAP.md` — map the BOM into the first hub schematic
- `RECOMMENDED-FIRST-CAPTURE.md` — the recommended first board scope
- `../FIRST-BOARD-CHECKLIST.md` — the execution checklist that decides when this
  packet is allowed to move on to secondary variants

## Capture Order

1. Native USB path and `VBUS_5V` entry from the connector
2. `RT9080-33GJ5` 5V-to-3.3V regulation, decoupling, and connector-side protection
3. Boot/reset and bring-up access
4. Status LED and any test pads

## First Board Reality

- The current PCB outline is stepped: the USB-A nose carries the SOFNG USB-05
  shell-tab pads and widens to a `54 x 26 mm` module/service body behind the
  plug. That is more honest than the earlier placeholder, but adjacent-port
  host clearance is now an explicit mechanical risk to verify.
- `R1` is resolved as two 22R 0402 resistors (`R1A`, `R1B`) placed at the
  ESP32-S3 side of the native USB pair. `C5` / `C6` remain unconnected
  no-BOM 0402 mechanical placeholders in this pass; shunt capacitors are not
  part of the clean first-board routing until SI evidence calls for them.
- `U1` is rotated so the ESP32-S3 antenna keep-out lands at the rear of the
  dongle, away from the USB shell and away from service pads.
- `SW1` is a pad-actuated `BOOT_N` service path for this pass; `EN`, `BOOT_N`,
  UART0, power, and ground pads remain probeable along the reopenable seam.
  USB data continuity is inspected at trace/connector access points rather than
  dedicated connected USB data service pads in this pass. `TP6`-`TP9` are now
  explicit no-BOM schematic service pads matching the routed board footprints.
- The schematic now carries the routed board's common ground, EN RC support,
  status LED path, and local decoupling instead of leaving those as PCB-only
  drift. The USB shell tabs and ESP32-S3 module ground pads are now explicit
  schematic pins tied to ground, and PCB footprint metadata matches the locked
  schematic fields. KiCad CLI verification is active on this packet: the current
  schematic ERC and PCB DRC pass at error severity with local symbol and
  footprint libraries loaded, the all-severity schematic ERC reports 0
  messages, and the all-severity PCB DRC pass is clean with 0 unconnected items
  and 0 schematic parity issues.
  `usb_hub.kicad_pro` intentionally ignores `lib_footprint_mismatch` because
  the first-board footprints are now source-controlled in
  `PowerFinger_USB.pretty/`; the remaining blockers are measured hardware
  evidence, not KiCad ERC/DRC drift.
- Local fabrication-review outputs are generated by
  `scripts/generate-usb-hub-fabrication-review.py` under
  `build-kicad/USB-HUB/fabrication-review/`. `FABRICATION-OUTPUTS.md` records
  the current output hashes and the active-BOM/POS review status; those outputs
  are reproducible review artifacts, not source-controlled fabrication release
  proof.

## Hard Constraints

- Native USB is load-bearing for the hub. Do not insert an unnecessary USB-UART
  bridge into the normal data path.
- Treat [PLACEMENT-CONSTRAINTS.md](PLACEMENT-CONSTRAINTS.md) as a blocker list.
- Connector mechanical support matters as much as the schematic.
- `VREG_3V3` must be generated by the captured board power tree, not borrowed
  from a hidden dev-board assumption.
- The current P0 path locks `J1`, `U2`, and `D1`; those exact parts are now
  represented in schematic and PCB source.
- `usb_and_power.kicad_sch` now contains the locked USB/power symbols plus the
  `R1A` / `R1B` 22R native-USB decision.
- The first PCB source captures connector reinforcement geometry, but that is
  not a substitute for the retention evidence in
  `../CONNECTOR-RETENTION-VERIFY.md`.
- Close `../FIRST-BOARD-CHECKLIST.md` and
  `../CONNECTOR-RETENTION-VERIFY.md` before treating this lane as hardware-ready.

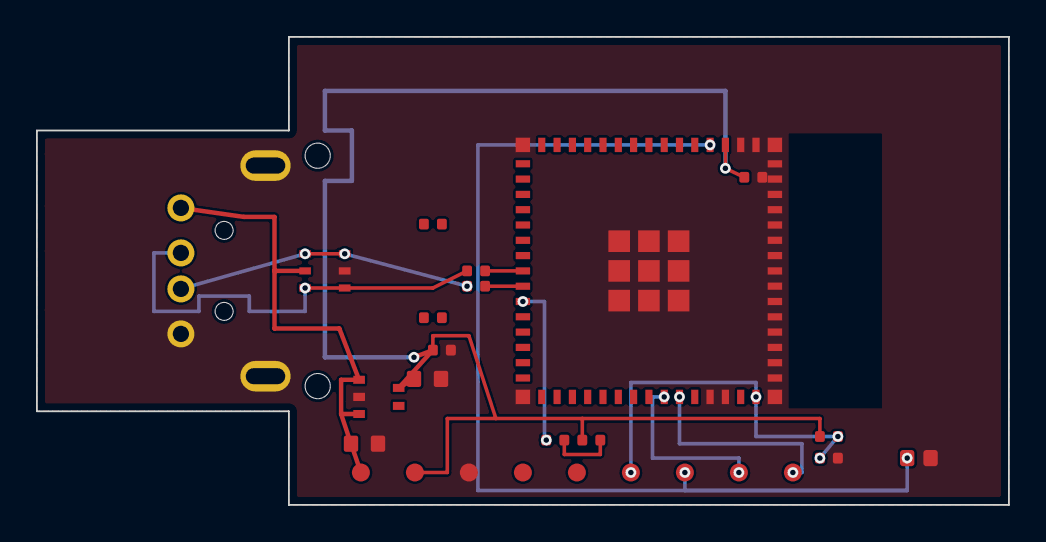
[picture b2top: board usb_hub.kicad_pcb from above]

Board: 2 copper layers, 54.0 x 26.0 mm, 28 parts (0 on the bottom side), 13 nets.

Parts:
C1A, C1B: 100nF; C_0402_1005Metric_FirstBoard
C2: 10uF; C_0603_1608Metric_FirstBoard
C3: 1uF; C_0603_1608Metric_FirstBoard
C4: 1uF; C_0402_1005Metric_FirstBoard
C5: DNI USB_D- no-net; C_0402_1005Metric_FirstBoard
C6: DNI USB_D+ no-net; C_0402_1005Metric_FirstBoard
D1: USBLC6-2SC6; SOT-23-6_FirstBoard
J1: SOFNG USB-05; USB_A_Plug_SOFNG_USB-05
LED1: green; LED_0402_1005Metric_FirstBoard
MH1, MH2: shell clamp; MountingHole_1.4mm_Clamp
R1A, R1B: 22R; R_0402_1005Metric_FirstBoard
R2: 1k; R_0402_1005Metric_FirstBoard
R3: 10k; R_0402_1005Metric_FirstBoard
SW1: BOOT_SERVICE; PadActuated_Boot_Service
TP1: VBUS; TestPoint_Pad_D1.0mm_FirstBoard
TP2: 3V3; TestPoint_Pad_D1.0mm_FirstBoard
TP3: GND; TestPoint_Pad_D1.0mm_FirstBoard
TP4: D- trace access; TestPoint_Pad_D1.0mm_FirstBoard
TP5: D+ trace access; TestPoint_Pad_D1.0mm_FirstBoard
TP6: EN; TestPoint_Pad_D1.0mm_FirstBoard
TP7: BOOT; TestPoint_Pad_D1.0mm_FirstBoard
TP8: TX; TestPoint_Pad_D1.0mm_FirstBoard
TP9: RX; TestPoint_Pad_D1.0mm_FirstBoard
U1: ESP32-S3-MINI-1-N8; ESP32-S3-MINI-1-N8_FirstBoard
U2: RT9080-33GJ5; SOT-23-5_FirstBoard

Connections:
/controls_and_indicators/BOOT_N: SW1.1, TP7.1, U1.4
/controls_and_indicators/EN: C4.1, R3.2, TP6.1, U1.45
/controls_and_indicators/GND: C1A.2, C1B.2, C2.1, C3.1, C4.2, D1.2, J1.4, J1.SH1, J1.SH2, SW1.2, TP3.1, U1.1, U1.2, U1.42, U1.43, U1.46, U1.47, U1.48, U1.49, U1.50, U1.51, U1.52, U1.53, U1.54, U1.55, U1.56, U1.57, U1.58, U1.59, U1.60, U1.61, U1.62, U1.63, U1.64, U1.65, U2.2
/controls_and_indicators/LED_LIMIT: LED1.2, R2.2
/controls_and_indicators/LED_STATUS: LED1.1, U1.25
/controls_and_indicators/UART_RX_DBG: TP9.1, U1.40
/controls_and_indicators/UART_TX_DBG: TP8.1, U1.39
/controls_and_indicators/VREG_3V3: C1A.1, C1B.1, C3.2, R2.1, R3.1, TP2.1, U1.3, U2.5
/mcu_radio/USB_D+: R1B.2, U1.24
/mcu_radio/USB_D-: R1A.2, U1.23
/usb_and_power/USB_D+_CONN: D1.3, D1.4, J1.3, R1B.1
/usb_and_power/USB_D-_CONN: D1.1, D1.6, J1.2, R1A.1
/usb_and_power/VBUS_5V: C2.2, D1.5, J1.1, TP1.1, U2.1, U2.3

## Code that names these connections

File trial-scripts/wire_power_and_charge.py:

# SPDX-License-Identifier: MIT
"""Trial driver: wire R30 power_and_charge sub-sheet via kicad-sch-api.

Strategy: place a wire label at every component pin position, naming the
net. KiCad treats same-named labels on a sheet as one net. Hierarchical
labels (VBUS_5V, VREG_3V3, VBAT_SENSE, NTC_SENSE, CHARGE_EN) already exist
and are matched by name.

Internal nets:
  VBUS_CHG       — Q1.D → U3.VCC (TP4054 input via P-MOSFET high-side switch)
  Q1_GATE        — Q1.G ← R4 pull-up to VBUS_5V; Q2.D pulls low when CHARGE_EN
  VBAT_PROTECTED — TP4054.BAT → battery rail → U4.VIN/EN, divider tops
  U3_PROG        — TP4054.PROG → R1 → GND (charge current set)
  CHRG_STAT_INT  — TP4054.STAT (open-drain) → R11 pull-up to VREG_3V3
  VBUS_DETECT_INT — R9/R10 divider mid-point (no parent sheet pin yet)
"""
from __future__ import annotations

import sys
from pathlib import Path

import kicad_sch_api as ksa

SHEET = (
    "hardware/ring/R30-OLED-NONE-NONE/kicad/sheets/power_and_charge.kicad_sch"
)

# (ref, pin_number, net_name) — None means leave unconnected (NC pin)
TOPOLOGY = [
    # Q1 — P-MOSFET high-side switch (S=VBUS_5V, D=VBUS_CHG, G=Q1_GATE)
    ("Q1", "S", "VBUS_5V"),
    ("Q1", "D", "VBUS_CHG"),
    ("Q1", "G", "Q1_GATE"),
    # Q2 — N-MOSFET low-side gate driver
    ("Q2", "D", "Q1_GATE"),
    ("Q2", "S", "GND"),
    ("Q2", "G", "CHARGE_EN"),
    # R4 — Q1 gate pull-up to VBUS_5V (default-off)
    ("R4", "1", "VBUS_5V"),
    ("R4", "2", "Q1_GATE"),
    # R6 — Q2 gate pulldown to GND (default-off)
    ("R6", "1", "CHARGE_EN"),
    ("R6", "2", "GND"),
    # U3 — TP4054 (MCP73831-2-OT pinout: STAT=1, VSS=2, VBAT=3, VDD=4, PROG=5)
    ("U3", "1", "CHRG_STAT_INT"),
    ("U3", "2", "GND"),
    ("U3", "3", "VBAT_PROTECTED"),
    ("U3", "4", "VBUS_CHG"),
    ("U3", "5", "U3_PROG"),
    # R1 — TP4054 charge current set (20k → ~50mA)
    ("R1", "1", "U3_PROG"),
    ("R1", "2", "GND"),
    # R11 — CHRG_STAT pull-up
    ("R11", "1", "VREG_3V3"),
    ("R11", "2", "CHRG_STAT_INT"),
    # U4 — RT9080 LDO (AP2112K pinout: VIN=1, GND=2, EN=3, NC=4, VOUT=5)
    ("U4", "1", "VBAT_PROTECTED"),
    ("U4", "2", "GND"),
    ("U4", "3", "VBAT_PROTECTED"),  # EN tied to VIN (always enabled)
    # U4.4 = NC, intentionally unlabeled
    ("U4", "5", "VREG_3V3"),
    # C1 — TP4054 input decoupling
    ("C1", "1", "VBUS_CHG"),
    ("C1", "2", "GND"),
    # C2 — LDO input bulk
    ("C2", "1", "VBAT_PROTECTED"),
    ("C2", "2", "GND"),
    # C3 — LDO output decoupling
    ("C3", "1", "VREG_3V3"),
    ("C3", "2", "GND"),
    # R7/R8 — VBAT_SENSE divider (100k/100k, top to VBAT_PROTECTED)
    ("R7", "1", "VBAT_PROTECTED"),
    ("R7", "2", "VBAT_SENSE"),
    ("R8", "1", "VBAT_SENSE"),
    ("R8", "2", "GND"),
    # R9/R10 — VBUS_DETECT divider (220k/100k, top to VBUS_5V)
    ("R9", "1", "VBUS_5V"),
    ("R9", "2", "VBUS_DETECT_INT"),
    ("R10", "1", "VBUS_DETECT_INT"),
    ("R10", "2", "GND"),
    # R3 — NTC divider top from VREG_3V3
    ("R3", "1", "VREG_3V3"),
    ("R3", "2", "NTC_SENSE"),
    # NTC1 — divider bottom to GND
    ("NTC1", "1", "NTC_SENSE"),
    ("NTC1", "2", "GND"),
]


def main() -> int:
    repo = Path(__file__).resolve().parent.parent
    sheet_path = repo / SHEET
    sch = ksa.load_schematic(str(sheet_path))
    print(f"loaded {sheet_path}")

    # collect U4 NC pin position so a no-connect marker can be placed
    nc_pos = None
    for p_num, p_pos in sch.list_component_pins("U4"):
        if p_num == "4":
            nc_pos = p_pos
            break

    placed = 0
    for ref, pin, net in TOPOLOGY:
        try:
            pos = sch.get_component_pin_position(ref, pin)
        except Exception as exc:
            print(f"  FAIL  pin lookup {ref}.{pin}: {exc!r}", file=sys.stderr)
            return 3
        if pos is None:
            print(f"  FAIL  no pin position for {ref}.{pin}", file=sys.stderr)
            return 3
        sch.add_label(net, position=(pos.x, pos.y))
        placed += 1
        print(f"  label {net:18s} at {ref}.{pin} ({pos.x:.2f}, {pos.y:.2f})")

    # Add a no-connect marker on U4.NC if API supports it; otherwise skip
    # (kicad-sch-api may not expose no_connect — the NC pin will register as
    # pin_not_connected, which is correct semantics for a true NC pin)
    if nc_pos is not None and hasattr(sch, "add_no_connect"):
        try:
            sch.add_no_connect(position=(nc_pos.x, nc_pos.y))
            print(f"  no-connect at U4.4 ({nc_pos.x:.2f}, {nc_pos.y:.2f})")
        except Exception as exc:
            print(f"  WARN  no_connect not supported: {exc!r}", file=sys.stderr)

    sch.save()
    print(f"saved. placed {placed} labels.")
    return 0


if __name__ == "__main__":
    sys.exit(main())

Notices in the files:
hardware/ring/R30-OLED-NONE-NONE/kicad/r30_oled_none_none.kicad_pcb:
CERN-OHL-S-2.0 hardware source
